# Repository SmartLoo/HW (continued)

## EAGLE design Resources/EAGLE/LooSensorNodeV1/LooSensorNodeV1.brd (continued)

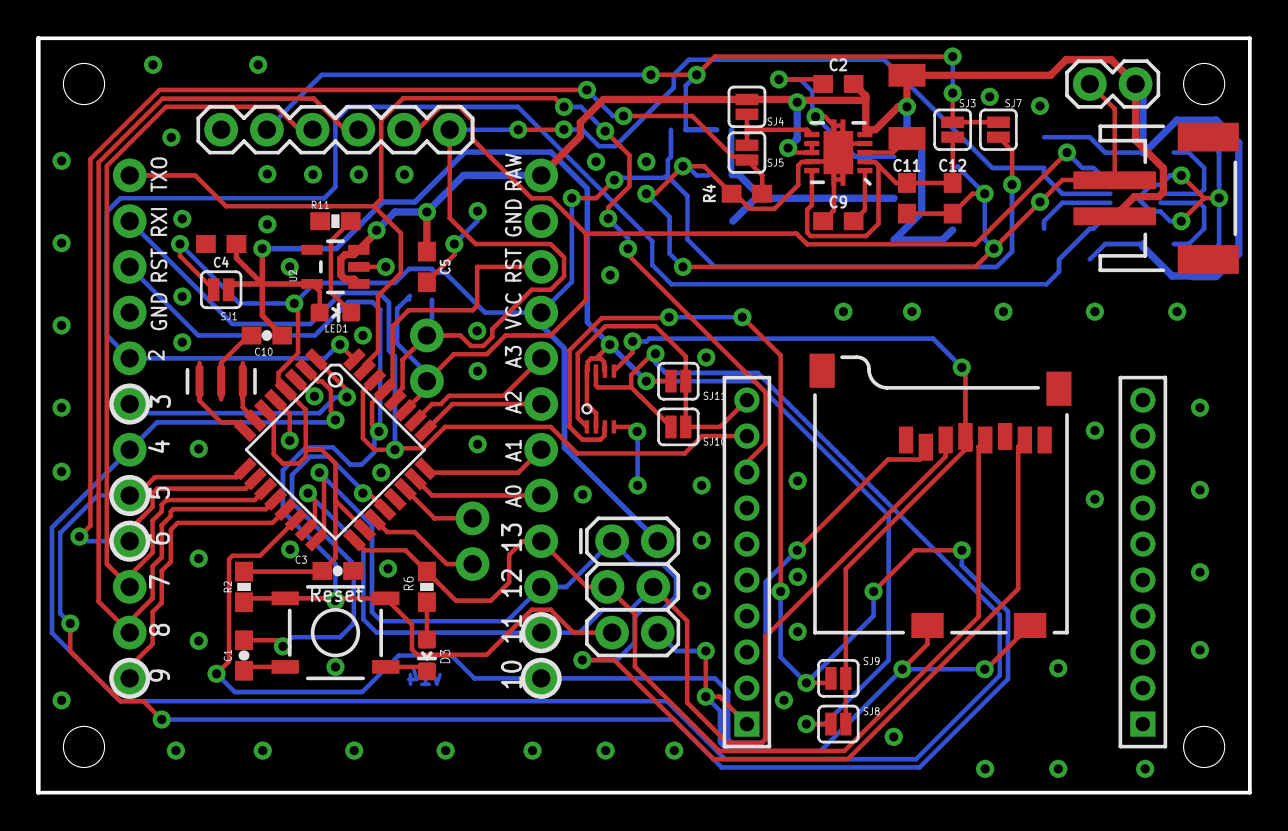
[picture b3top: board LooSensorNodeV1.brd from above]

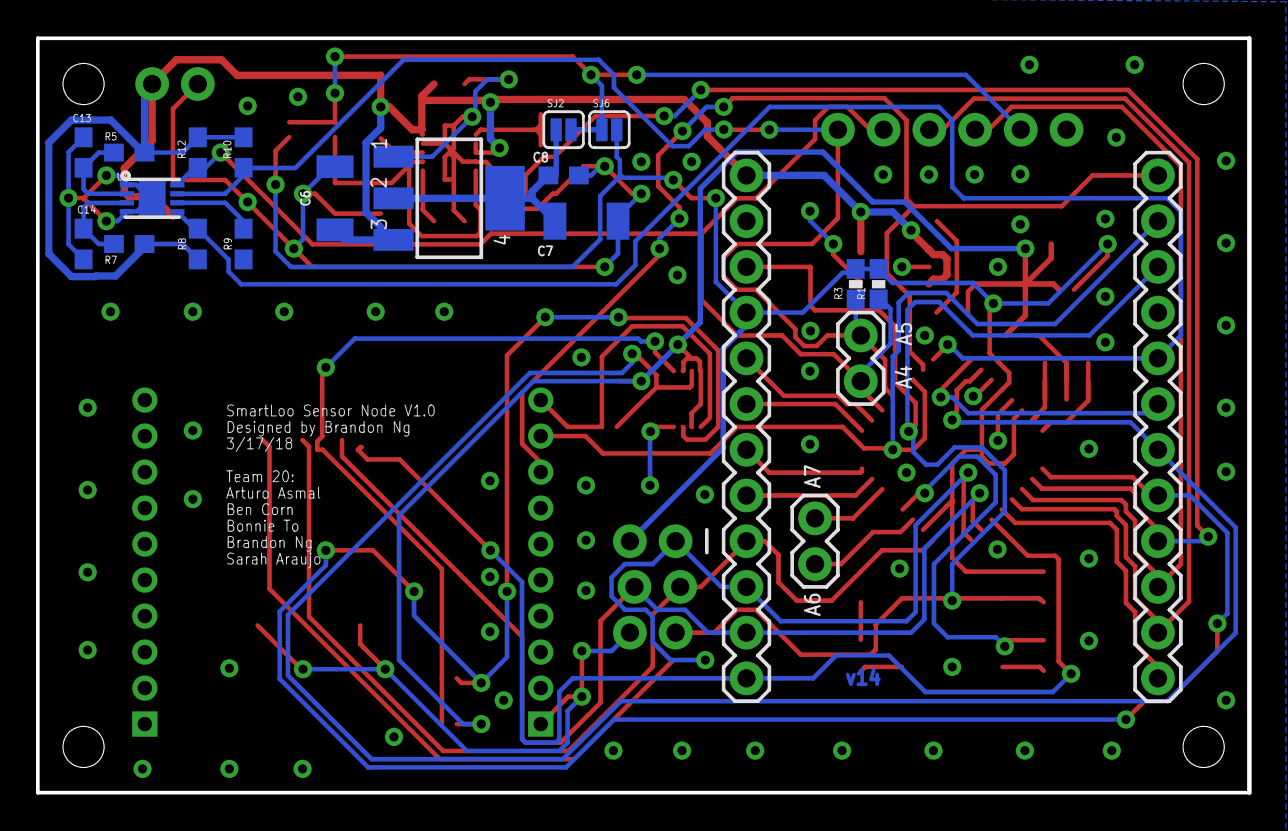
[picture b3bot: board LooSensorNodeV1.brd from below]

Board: 2 copper layers, 67.3 x 41.9 mm, 60 parts (21 on the bottom side), 43 nets.

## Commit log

2017-11-16 hello comment
2018-02-07 Updating POST request given updated API format.
2018-02-07 String parsing for new format of data
    String parsing for GUID, Sensor Value, and Battery Level
2018-02-07 Update API endpoint for new sensor update
2018-02-08 Updating function signature to match new types
2018-02-08 Update transmitter code to include guid and alter output format
2018-02-08 Fixing variable names
2018-02-08 Updating request string
2018-02-11 XBee dedicated serial channel, error corrections
2018-02-15 Code working 2/15
2018-03-27 Create ESP32toAPI
    Changed for the ESP32. Will need to remap HardwareSerial.cpp file from pins 9/10 to 4/2.
2018-03-27 Rename ESP32toAPI to ESP32toAPI.ino
2018-04-01 commiting esp32 code as working.
    using D4 pin as TX , RX2 as RX.
2018-04-03 Update Measure_angle_Arduino_MPU6050.ino
    Updated serial.begin(115200)
2018-04-03 Update Measure_angle_Arduino_MPU6050.ino
    port 7, 8
2018-04-05 Updated US
2018-04-23 incorporated watch dog timer power optimization code
2018-04-26 modified WDT control code and return message format
2018-04-26 change logic for when to check ultrasonic reading
2018-04-27 code cleanup and correct message format
2018-04-27 code cleanup for water sensor code and introduced WDT optimization to water sensor code
2018-04-29 adding resource files
2018-04-30 including SmartLoo EAGLE Library
2018-04-30 including BOM
2018-04-30 adding Readme
2018-05-01 inital commit of soap dispenser sketch
2018-05-03 add alternative sleep method
2018-05-03 adjust message format
2018-05-03 update soap sensor timing
2018-05-04 update tracker logic
2018-05-04 fix tracker logic
2018-05-04 Update esp32wifi.ino
    Updated to meet new database string format.
